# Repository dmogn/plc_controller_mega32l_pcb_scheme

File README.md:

# plc_controller_mega32l

PLC controller hardware PCB scheme. ATMega32L, RS485 industrial bus interface, 8 ADC inputs, 8 PWM out, 6 GPIO

KiCAD 5.1 project.

Status: Alpha

**Features:**

- Discrete diode protection for high & low overvoltage for all input & interface contacs.

- Two types of RS485 input connectors (1*RJ-45, 3*RJ-11).

- Output RS485 RJ-11 connectors. The controller can act as connection hub on RS485 network with tree-like topology. Up to 3 output connections.

- Up to 2 Mbps RS485 bus speed. 

- JTAG debug interface.

- 5 to 25V power supply.

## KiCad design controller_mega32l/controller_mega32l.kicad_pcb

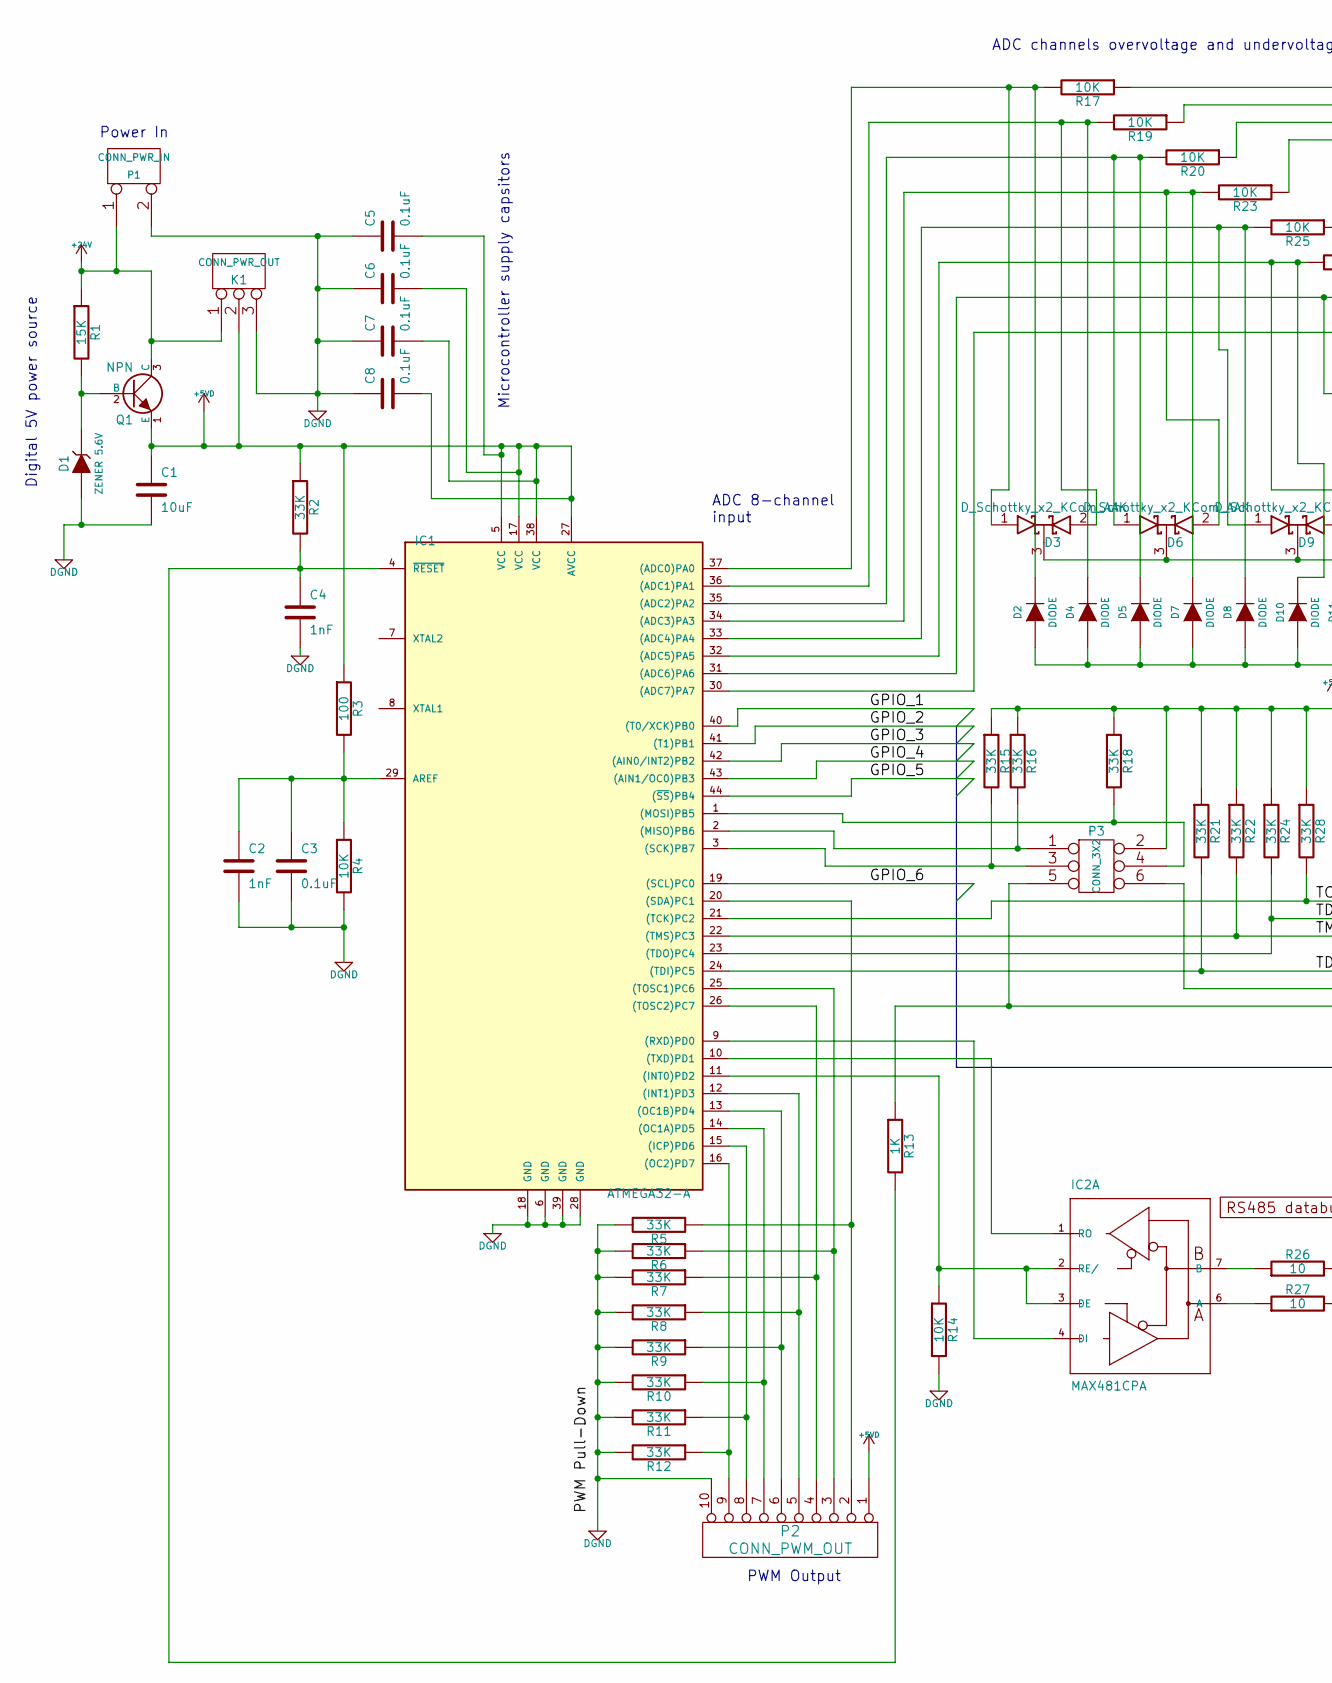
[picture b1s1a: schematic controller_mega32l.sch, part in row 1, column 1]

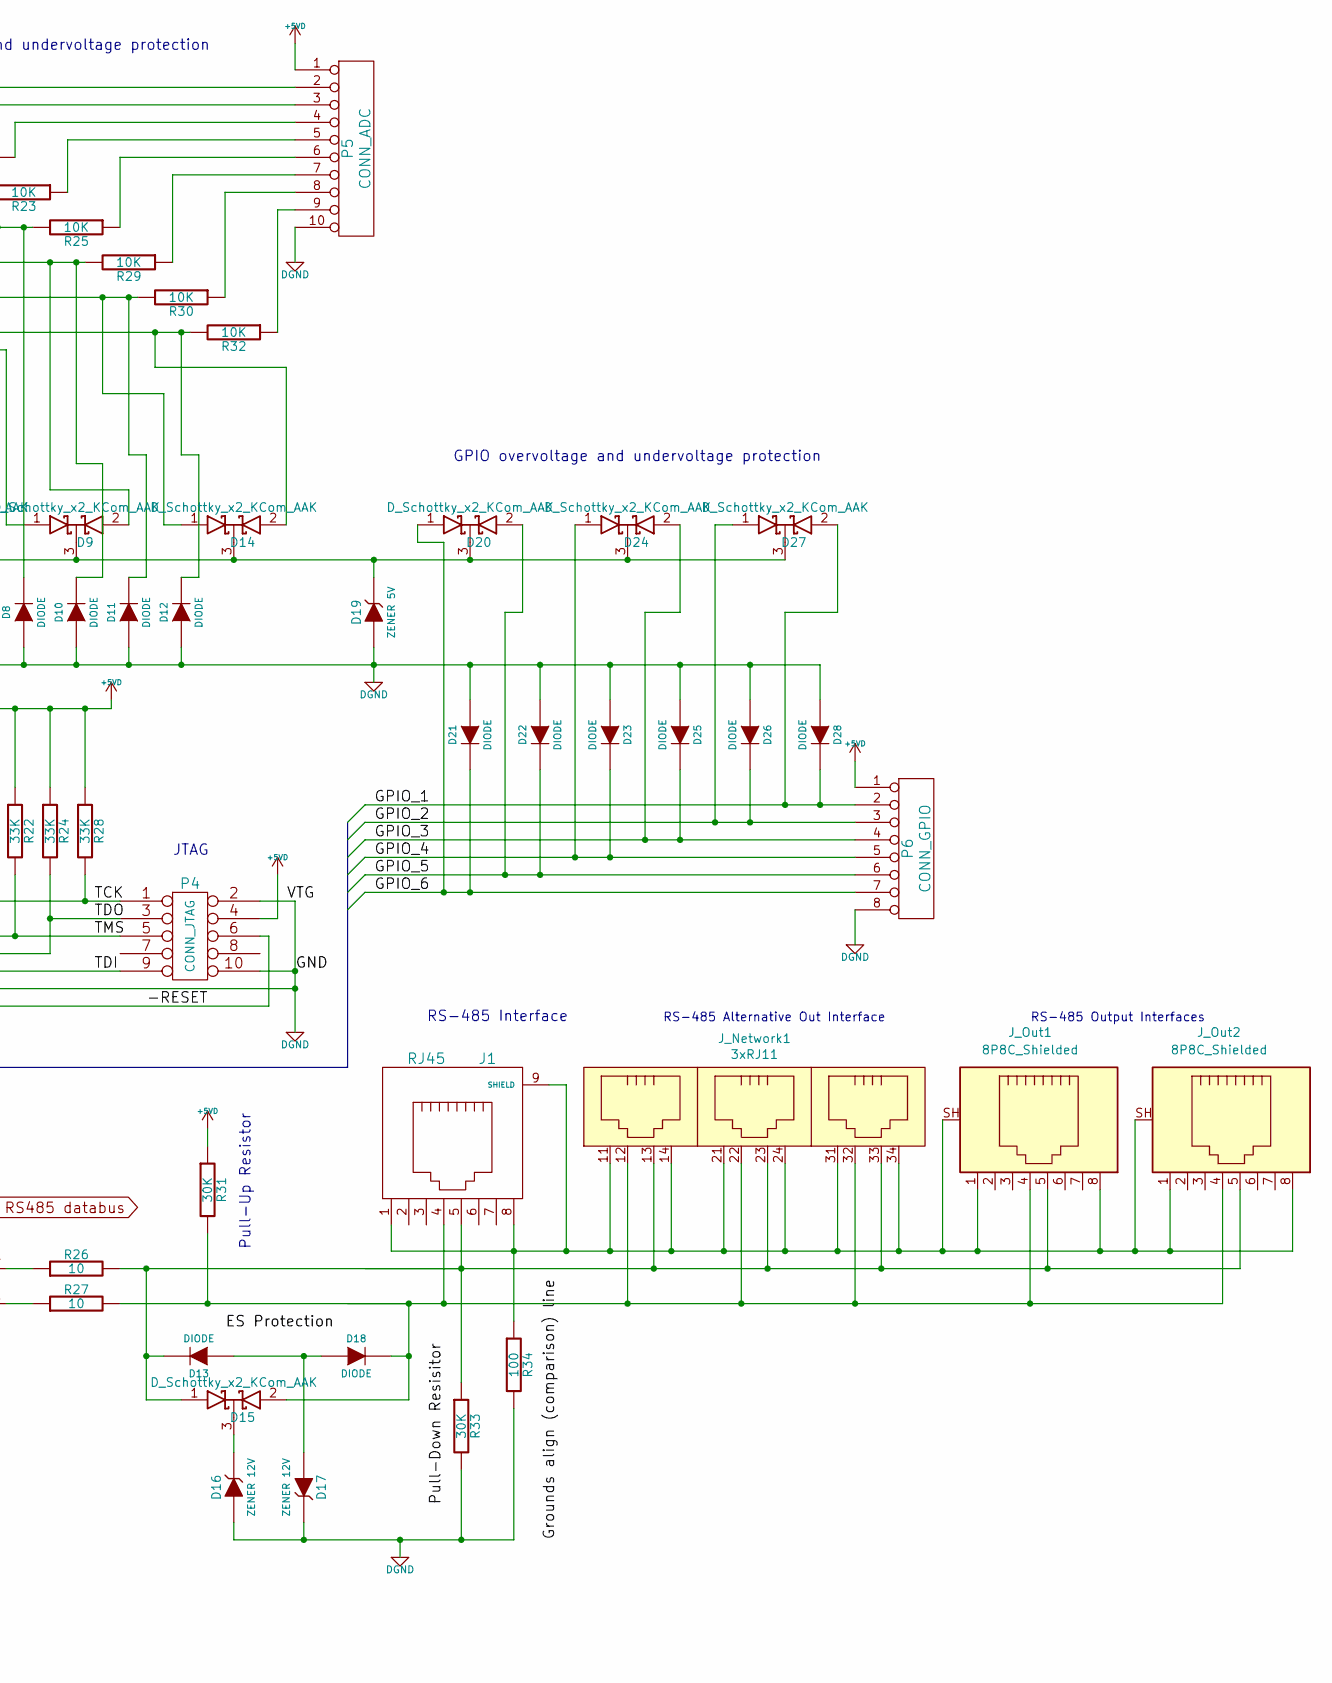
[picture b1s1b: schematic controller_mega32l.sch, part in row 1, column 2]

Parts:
C1: 10uF; SM1210
C2, C4: 1nF; SM0805
C3, C5, C6, C7, C8: 0.1uF; SM0805
D1: ZENER 5.6V; SM1210L
D2, D4, D5, D7, D8, D10, D11, D12, D13, D18, D23, D25, D26, D28: DIODE; SOT23
D3, D6, D9, D14, D15, D24, D27: D_Schottky_x2_KCom_AAK; SOT23
D16, D17: ZENER 12V; SOT23
D19: ZENER 5V; SOT23
D20: D_Schottky_x2_KCom_AAK; SM1210L
D21, D22: DIODE; SM1206
IC1: ATMEGA32-A; TQFP44
IC2: MAX481CPA; DIP-8__300
J1: RJ45; RJ45_Amphenol_54602-x08_Horizontal
J_Network1: 3xRJ11
J_Out1, J_Out2: 8P8C_Shielded; RJ45_Amphenol_54602-x08_Horizontal
K1: CONN_PWR_OUT; PIN_ARRAY_3X1
P1: CONN_PWR_IN; PIN_ARRAY_5x2
P2: CONN_PWM_OUT; pin_array_3x2
P3: CONN_3X2; PIN_ARRAY_5x2
P4: CONN_JTAG; PIN_ARRAY_5x2
P5: CONN_ADC; pin_array_4x2
P6: CONN_GPIO; PIN_ARRAY_2X1
Q1: NPN; TO220
R1: 15K; C1
R2, R5, R6, R7, R8, R9, R10, R11, R12, R15, R16, R18, R21, R22, R24, R28: 33K; SM0603
R3, R34: 100; C1
R4, R14, R17, R19, R20, R23, R25, R29, R30, R32: 10K; C1
R13: 1K; C1
R26, R27: 10; C1
R31, R33: 30K; SM0603

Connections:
+5VD: C1.1, C5.2, C6.2, C7.2, C8.2, IC1.5 (VCC), IC1.17 (VCC), IC1.27 (AVCC), IC1.38 (VCC), K1.2 (PM), P2.1, P3.2, P4.4, P5.1, P6.1, Q1.1 (E), R2.1, R3.1, R15.1, R16.1, R18.1, R21.1, R22.1, R24.1, R28.1, R31.1
+24V: K1.1, P1.1, Q1.3 (C), R1.1
/-RESET: P3.5, P4.6, R13.1
/GPIO_1: D27.2 (A), D28.2 (K), IC1.40 ((T0/XCK)PB0), P6.2
/GPIO_2: D26.2 (K), D27.1 (A), IC1.41 ((T1)PB1), P6.3
/GPIO_3: D24.2 (A), D25.2 (K), IC1.42 ((AIN0/INT2)PB2), P6.4
/GPIO_4: D23.2 (K), D24.1 (A), IC1.43 ((AIN1/OC0)PB3), P6.5
/GPIO_5: D20.2 (A), D22.2 (K), IC1.44 ((~SS~)PB4), P6.6
/GPIO_6: D20.1 (A), D21.2 (K), IC1.19 ((SCL)PC0), P6.7
/TCK: IC1.21 ((TCK)PC2), P4.1, R28.2
/TDI: IC1.24 ((TDI)PC5), P4.9, R21.2
/TDO: IC1.23 ((TDO)PC4), P4.3, R24.2
/TMS: IC1.22 ((TMS)PC3), P4.5, R22.2
DGND: C1.2, C2.2, C3.2, C4.2, C5.1, C6.1, C7.1, C8.1, D1.1 (A), D2.1 (A), D4.1 (A), D5.1 (A), D7.1 (A), D8.1 (A), D10.1 (A), D11.1 (A), D12.1 (A), D16.1 (A), D17.2 (K), D19.1 (A), D21.1 (A), D22.1 (A), D23.1 (A), D25.1 (A), D26.1 (A), D28.1 (A), IC1.6 (GND), IC1.18 (GND), IC1.28 (GND), IC1.39 (GND), K1.3, P1.2 (PM), P2.10, P3.6, P4.2, P4.10, P5.10, P6.8, R4.2, R5.2, R6.2, R7.2, R8.2, R9.2, R10.2, R11.2, R12.2, R14.2, R33.2, R34.2
unnamed: C2.1, C3.1, IC1.29 (AREF), R3.2, R4.1
unnamed: C4.1, IC1.4 (~RESET), R2.2, R13.2
unnamed: D1.2 (K), Q1.2 (B), R1.2
unnamed: D2.2 (K), D3.1 (A), IC1.37 ((ADC0)PA0), R17.2
unnamed: D3.2 (A), D4.2 (K), IC1.36 ((ADC1)PA1), R19.2
unnamed: D5.2 (K), D6.1 (A), IC1.35 ((ADC2)PA2), R20.2
unnamed: D6.2 (A), D7.2 (K), IC1.34 ((ADC3)PA3), R23.2
unnamed: D8.2 (K), D9.1 (A), IC1.33 ((ADC4)PA4), R25.2
unnamed: D9.2 (A), D10.2 (K), IC1.32 ((ADC5)PA5), R29.2
unnamed: D11.2 (K), D14.1 (A), IC1.31 ((ADC6)PA6), R30.2
unnamed: D12.2 (K), D14.2 (A), IC1.30 ((ADC7)PA7), R32.2
unnamed: D13.1 (A), D17.1 (A), D18.1 (A)
unnamed: D13.2 (K), D15.1 (A), J1.5, J_Network1.13, J_Network1.23, J_Network1.33, J_Out1.5, J_Out2.5, R26.2, R33.1
unnamed: D3.3 (K), D6.3 (K), D9.3 (K), D14.3 (K), D19.2 (K), D20.3 (K), D24.3 (K), D27.3 (K)
unnamed: D15.2 (A), D18.2 (K), J1.4, J_Network1.12, J_Network1.22, J_Network1.32, J_Out1.4, J_Out2.4, R27.2, R31.2
unnamed: D15.3 (K), D16.2 (K)
unnamed: IC1.1 ((MOSI)PB5), P3.4, R18.2
unnamed: IC1.2 ((MISO)PB6), P3.1, R16.2
unnamed: IC1.3 ((SCK)PB7), P3.3, R15.2
unnamed: IC1.9 ((RXD)PD0), IC2.4 (DI)
unnamed: IC1.10 ((TXD)PD1), IC2.1 (RO)
unnamed: IC1.11 ((INT0)PD2), IC2.2 (RE/), IC2.3 (DE), R14.1
unnamed: IC1.12 ((INT1)PD3), P2.5, R8.1
unnamed: IC1.13 ((OC1B)PD4), P2.6, R9.1
unnamed: IC1.14 ((OC1A)PD5), P2.7, R10.1
unnamed: IC1.15 ((ICP)PD6), P2.8, R11.1
unnamed: IC1.16 ((OC2)PD7), P2.9, R12.1
unnamed: IC1.20 ((SDA)PC1), P2.2, R5.1
unnamed: IC1.25 ((TOSC1)PC6), P2.3, R6.1
unnamed: IC1.26 ((TOSC2)PC7), P2.4, R7.1
unnamed: IC2.6 (A), R27.1
unnamed: IC2.7 (B), R26.1
unnamed: J1.1, J1.8, J1.9 (SHIELD), J_Network1.11, J_Network1.14, J_Network1.21, J_Network1.24, J_Network1.31, J_Network1.34, J_Out1.1, J_Out1.8, J_Out1.SH, J_Out2.1, J_Out2.8, J_Out2.SH, R34.1
unnamed: P5.2, R17.1
unnamed: P5.3, R19.1
unnamed: P5.4, R20.1
unnamed: P5.5, R23.1
unnamed: P5.6, R25.1
unnamed: P5.7, R29.1
unnamed: P5.8, R30.1
unnamed: P5.9, R32.1

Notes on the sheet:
Power In
Digital 5V power source
Microcontroller supply capsitors
GPIO overvoltage and undervoltage protection
ADC channels overvoltage and undervoltage protection
JTAG
PWM Output
Pull-Up Resistor
RS-485 Interface
ADC 8-channel input
RS-485 Alternative Out Interface
RS-485 Output Interfaces

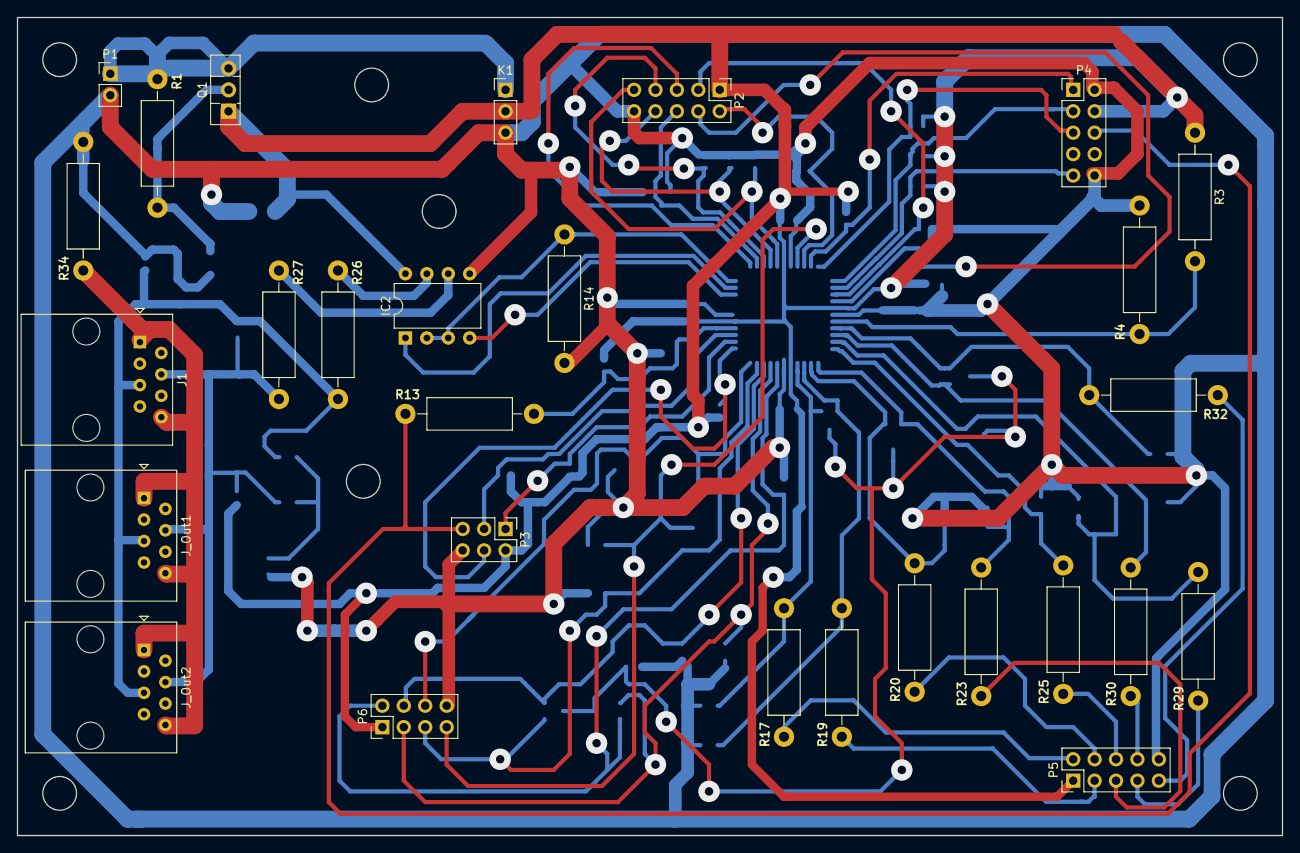
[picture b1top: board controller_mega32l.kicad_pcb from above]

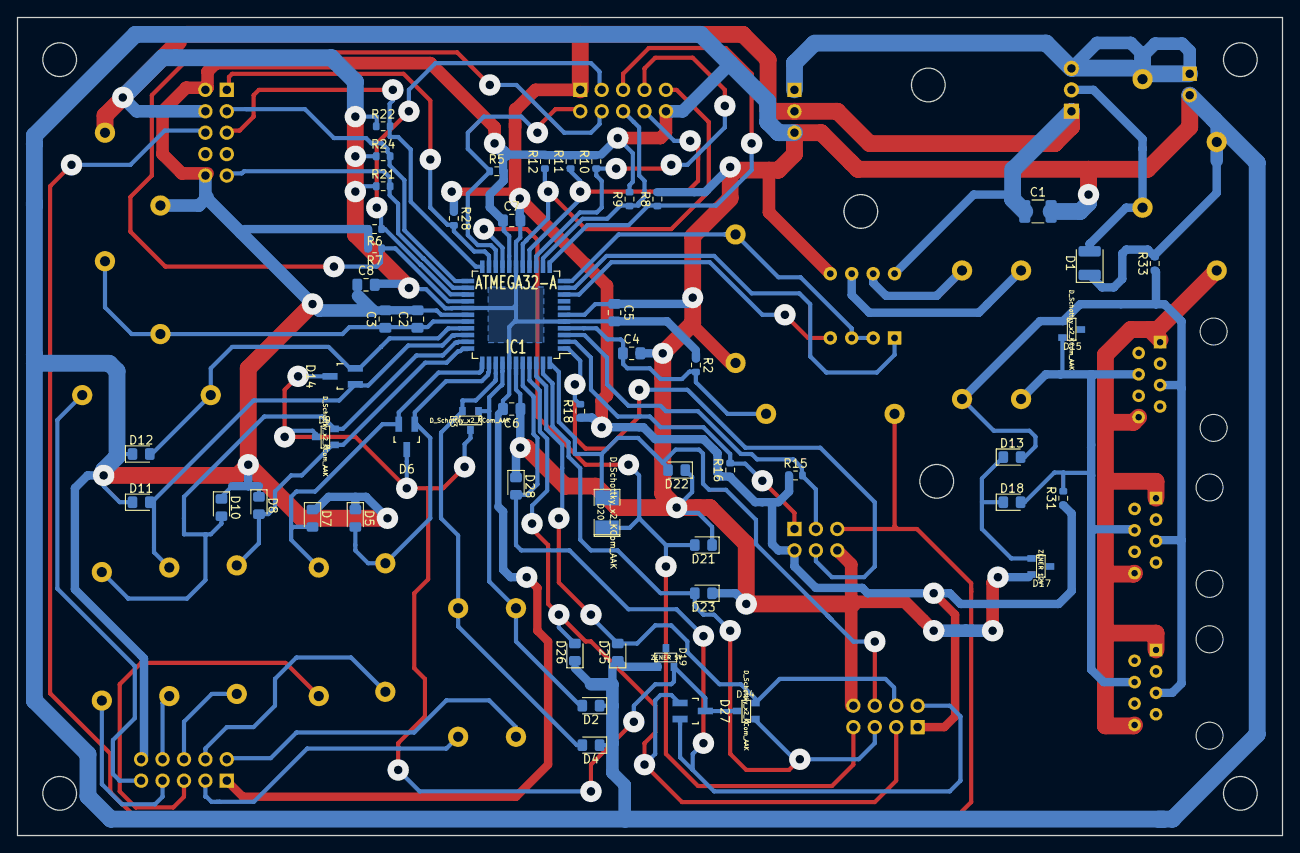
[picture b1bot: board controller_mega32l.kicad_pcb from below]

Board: 2 copper layers, 150.0 x 97.0 mm, 82 parts (54 on the bottom side), 54 nets.

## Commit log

2018-11-25 docs and scheme image added
2018-11-25 KiCAD project files initial commit
2019-06-07 PCB signal layer
2019-06-08 README features
2019-06-18 PCB changes
2021-01-07 New PCB routes, footprints updated, KiCAD up version to 5.1
2021-01-08 RJ-45 footprint updated, PCB screenshot added to docs
2021-01-08 RJ-45 ground connections fixed, PCB texts placed right
2021-01-08 PCB board outer dimensions added
2021-01-10 power lines optimization
2021-01-10 Output RJ-45 Interfaces added
